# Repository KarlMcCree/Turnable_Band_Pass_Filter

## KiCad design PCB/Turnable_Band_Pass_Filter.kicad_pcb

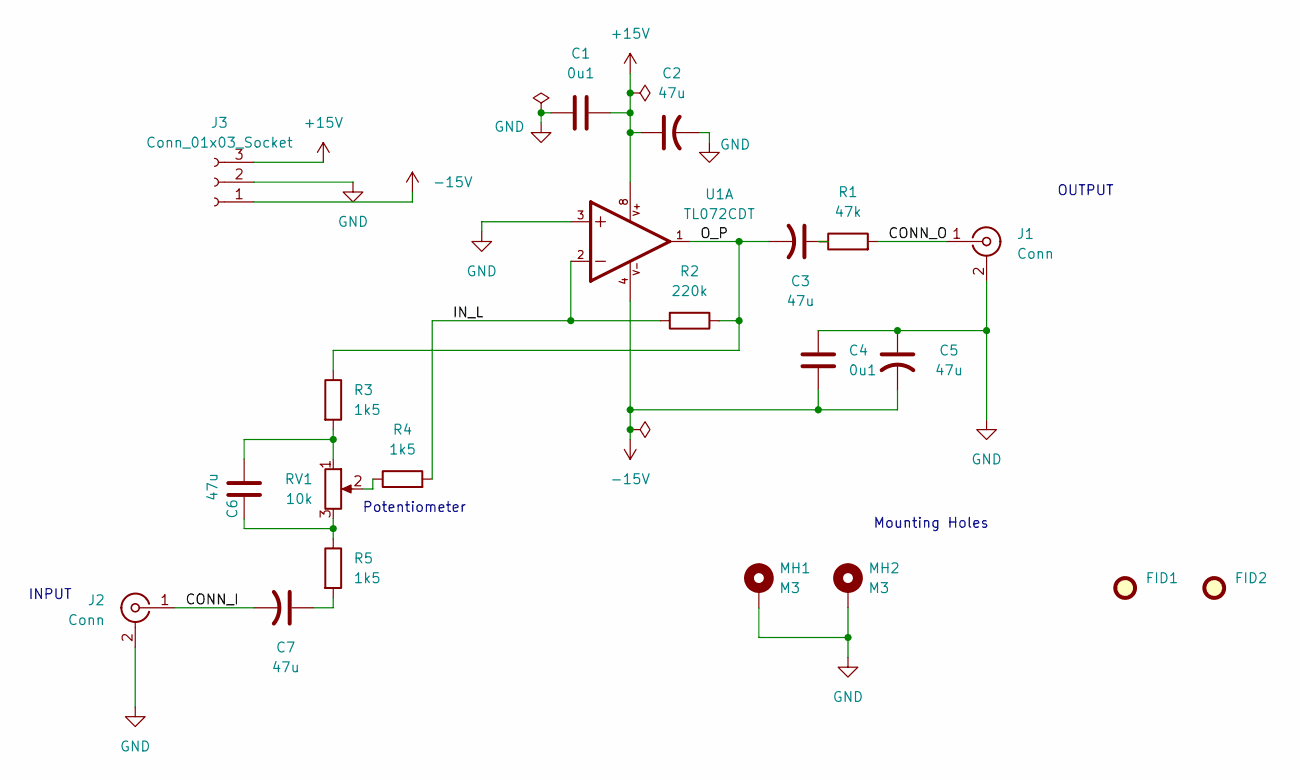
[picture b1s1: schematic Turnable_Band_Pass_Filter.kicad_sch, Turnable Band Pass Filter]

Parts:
C1, C4: 0u1; C_0805_2012Metric
C2, C3, C5, C7: 47u; CAP_EEE1CA470SP
C6: 47u; C_0805_2012Metric
FID1, FID2: Fiducial; Fiducial_0.5mm_Mask2mm
J1, J2: Conn; JST_B2B-ZR_LF__SN_
J3: Conn_01x03_Socket; HARWIN_M20-9990346
MH1, MH2: M3; MountingHole_3.2mm_M3_Pad_Via
R1: 47k; R_0805_2012Metric
R2: 220k; R_0805_2012Metric
R3, R4, R5: 1k5; R_0805_2012Metric
RV1: 10k; TRIM_3296W-1-203LF
U1: TL072CDT; SOIC127P600X175-8N; PARTREV 8

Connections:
+15V: C1.2, C2.1, J3.3, U1.8
-15V: C4.2, C5.2, J3.1, U1.4
/CONN_I: C7.2, J2.1 (In)
/CONN_O: J1.1 (In), R1.2
/IN_L: R2.2, R4.2, U1.2
/O_P: C3.2, R2.1, R3.1, U1.1
GND: C1.1, C2.2, C4.1, C5.1, J1.2 (Ext), J2.2 (Ext), J3.2, MH1.1, MH2.1, U1.3
unnamed: C3.1, R1.1
unnamed: C6.1, R5.1, RV1.3
unnamed: C6.2, R3.2, RV1.1
unnamed: C7.1, R5.2
unnamed: R4.1, RV1.2

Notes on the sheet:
Potentiometer
INPUT
Mounting Holes
OUTPUT

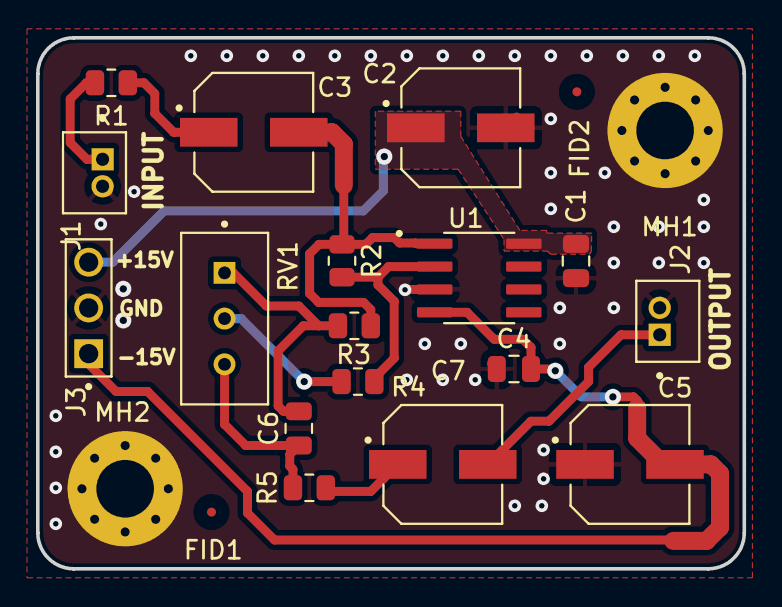
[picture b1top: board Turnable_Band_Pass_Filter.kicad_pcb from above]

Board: 2 copper layers, 39.2 x 29.5 mm, 21 parts (0 on the bottom side), 12 nets.
